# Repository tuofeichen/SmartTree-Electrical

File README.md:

# SmartTree Electrical System Design 
This repo contains the PCB design and Arduino code for the SmartTree electrical system. As a part of Engineers for a Sustainable World (ESW) at Northwestern, SmartTree is a student-run design project aimed to bring solar energy to Northwestern and get the community involved in sustainability. SmartTree provides a ‘trunk’ of solar-powered AC and USB outlets centered around a seating area, so anyone can bring his or her laptop or phone outside without having to worry about running low on battery. Having SmartTree on campus will not only allow students to best utilize technology outdoors, but also raise awareness for the potential solutions clean energy can bring to everyday life. Learn more about [ESW @ NU](http://www.eswnu.org/). 

The repo's directory is briefly described as below:

### Construction Documentation
contains the overall construction and design documentation, including hardware and software overview of the system. 

### BMS Software Documentation
contains the documentation for the battery management system software. It includes the design rationale of the software and some messaging protocal we use to communicate between the BMS board and the screen board. 

### PCB 
contains the PCB design of the battery management system (BMS) and the cell monitor unit (CMU), refer to the documentation for more details. 

### SmartTree Client
contains the client code of the software. The client is the microcontroller in charge of the screen update for the UI. It receives sensor data from the server and displays it on the screen. 

### SmartTree Server
contains the server code which controls and monitors the cell monitor unit and send out the information to the client for UI. 

### Testing
contains some the testing data logged on an SD card.

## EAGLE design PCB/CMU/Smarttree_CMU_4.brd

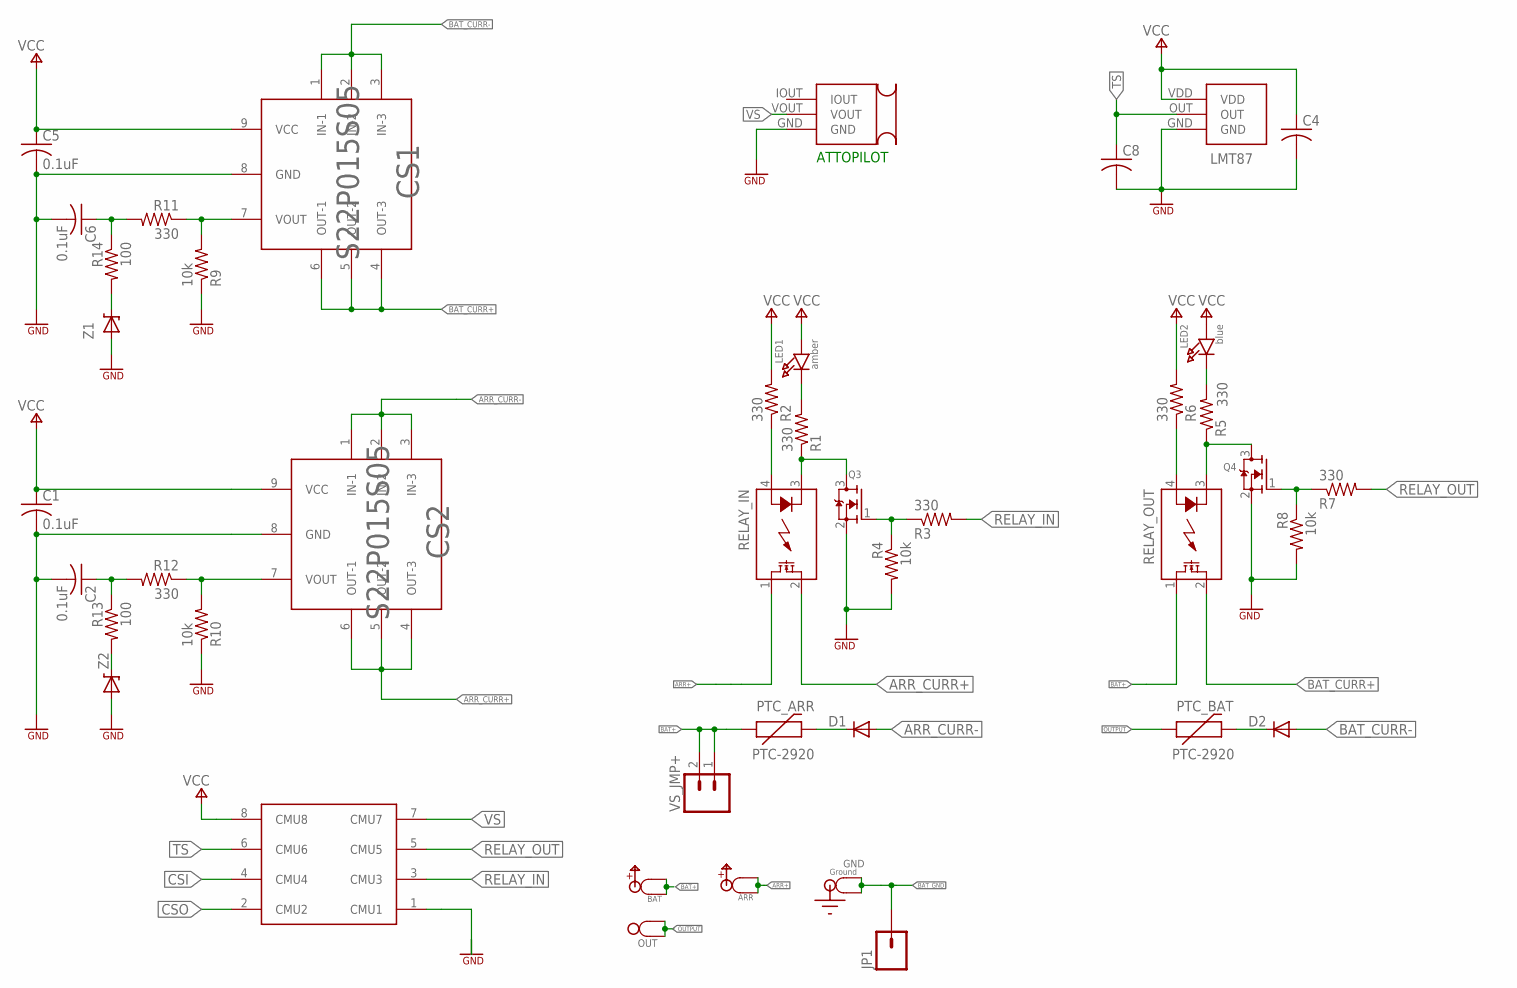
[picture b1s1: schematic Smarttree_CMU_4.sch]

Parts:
ARR: SPADE-POWER
ATTOPILOT: ATTOPILOT_VOLT; TH_BKOT
BAT: SPADE-POWER
C1, C2, C5, C6: 0.1uF; C0805
C4, C8: C-USC0805; C0805
CS1, CS2: S22P015S05
D1, D2: DIODE-SOD106-R; SOD106-R
GND: SPADE-GROUND
JP1: M01OFFSET; 1X01_OFFSET
LED1: amber; CHIPLED_0805
LED2: blue; CHIPLED_0805
LMT87: LMT87_PAC; LMT87_TO
OUT: SPADE-TERMINALPTH; SPADE-TERMINAL
PTC_ARR: PTC-2920
PTC_BAT: PTC-2920
Q3, Q4: MOSFET-NREFLOW; SOT23
R1, R2, R3, R5, R6, R7, R11, R12: 330; R0805
R4, R8, R9, R10: 10k; R0805
R13, R14: 100; R0805
RELAY_IN: CPC1708J; I4-PAC
RELAY_OUT: CPC1708J; I4-PAC
U$1: 8PINCONN
VS_JMP+: M02; 1X02_LONGPADS
Z1, Z2: DIODE-ZENER-BZT52; SOD-323

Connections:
ARR+: ARR.P$1, ARR.P$2, RELAY_IN.1 (DS1)
ARR_CURR+: CS2.4 (OUT-3), CS2.5 (OUT-2), CS2.6 (OUT-1), RELAY_IN.2 (DS2)
ARR_CURR-: CS2.1 (IN-1), CS2.2 (IN-2), CS2.3 (IN-3), D1.A
BAT+: BAT.P$1, BAT.P$2, PTC_ARR.1, RELAY_OUT.1 (DS1), VS_JMP+.1, VS_JMP+.2
BAT_CURR+: CS1.4 (OUT-3), CS1.5 (OUT-2), CS1.6 (OUT-1), RELAY_OUT.2 (DS2)
BAT_CURR-: CS1.1 (IN-1), CS1.2 (IN-2), CS1.3 (IN-3), D2.A
BAT_GND: GND.P$1, GND.P$2, JP1.1
CSI: C2.1, R12.2, R13.1, U$1.4 (CMU4)
CSO: C6.1, R11.2, R14.1, U$1.2 (CMU2)
GND: ATTOPILOT.GND, C1.2, C2.2, C4.2, C5.2, C6.2, C8.2, CS1.8 (GND), CS2.8 (GND), LMT87.GND, Q3.2 (S), Q4.2 (S), R4.2, R8.2, R9.1, R10.1, U$1.1 (CMU1), Z1.2 (A), Z2.2 (A)
unnamed: Q3.3 (D), R1.1, RELAY_IN.3 (K)
unnamed: Q4.3 (D), R5.1, RELAY_OUT.3 (K)
unnamed: LED1.C, R1.2
unnamed: R2.1, RELAY_IN.4 (A)
unnamed: LED2.C, R5.2
unnamed: Q3.1 (G), R3.1, R4.1
unnamed: R6.1, RELAY_OUT.4 (A)
unnamed: Q4.1 (G), R7.1, R8.1
unnamed: R13.2, Z2.1 (C)
unnamed: D2.C, PTC_BAT.2
unnamed: D1.C, PTC_ARR.2
unnamed: CS1.7 (VOUT), R9.2, R11.1
unnamed: CS2.7 (VOUT), R10.2, R12.1
unnamed: R14.2, Z1.1 (C)
OUTPUT: OUT.P$1, OUT.P$2, PTC_BAT.1
RELAY_IN: R3.2, U$1.3 (CMU3)
RELAY_OUT: R7.2, U$1.5 (CMU5)
TS: C8.1, LMT87.OUT, U$1.6 (CMU6)
VCC: C1.1, C4.1, C5.1, CS1.9 (VCC), CS2.9 (VCC), LED1.A, LED2.A, LMT87.VDD, R2.2, R6.2, U$1.8 (CMU8)
VS: ATTOPILOT.VOUT, U$1.7 (CMU7)

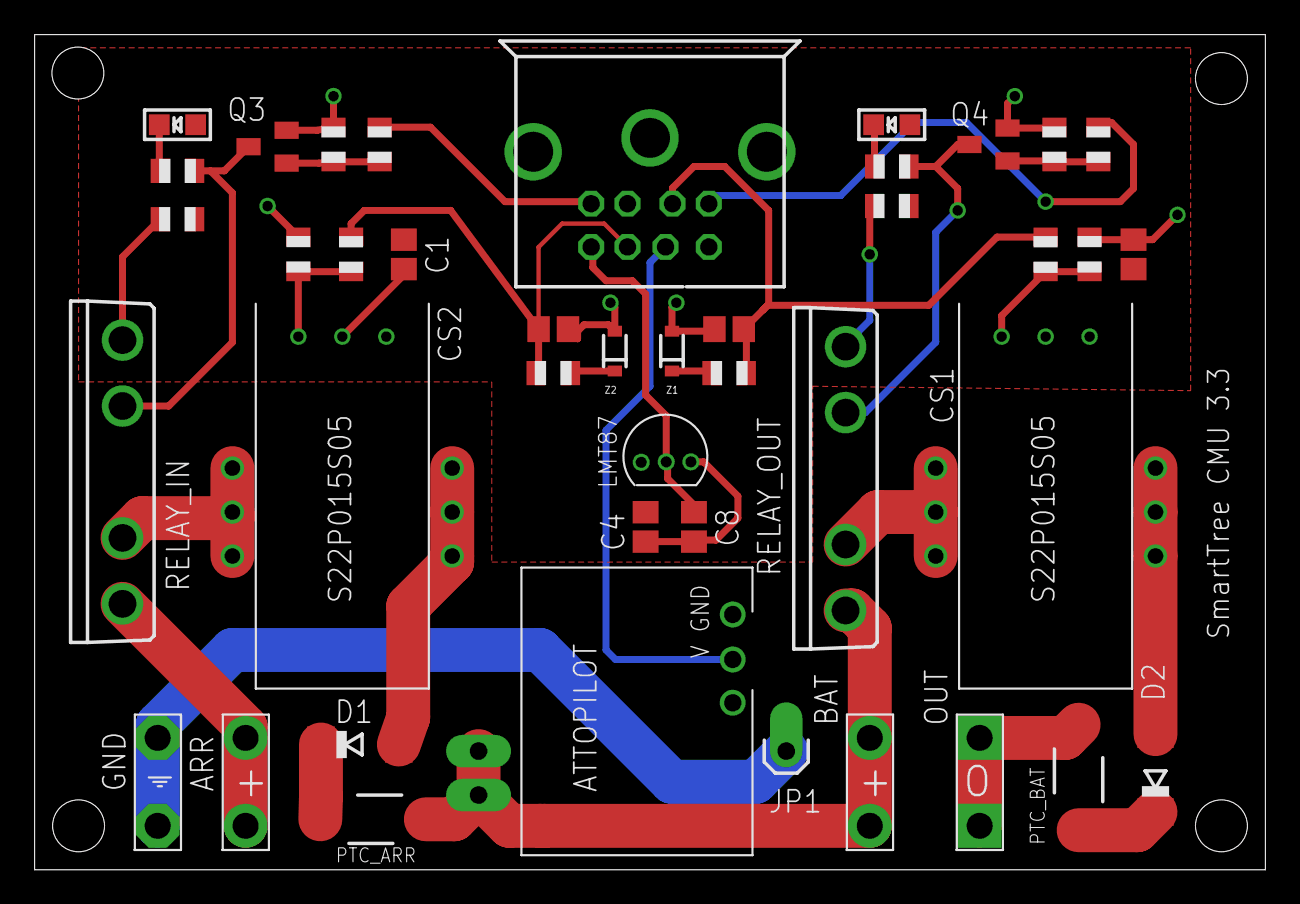
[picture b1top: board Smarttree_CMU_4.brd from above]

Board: 2 copper layers, 71.1 x 48.3 mm, 43 parts (0 on the bottom side), 30 nets.

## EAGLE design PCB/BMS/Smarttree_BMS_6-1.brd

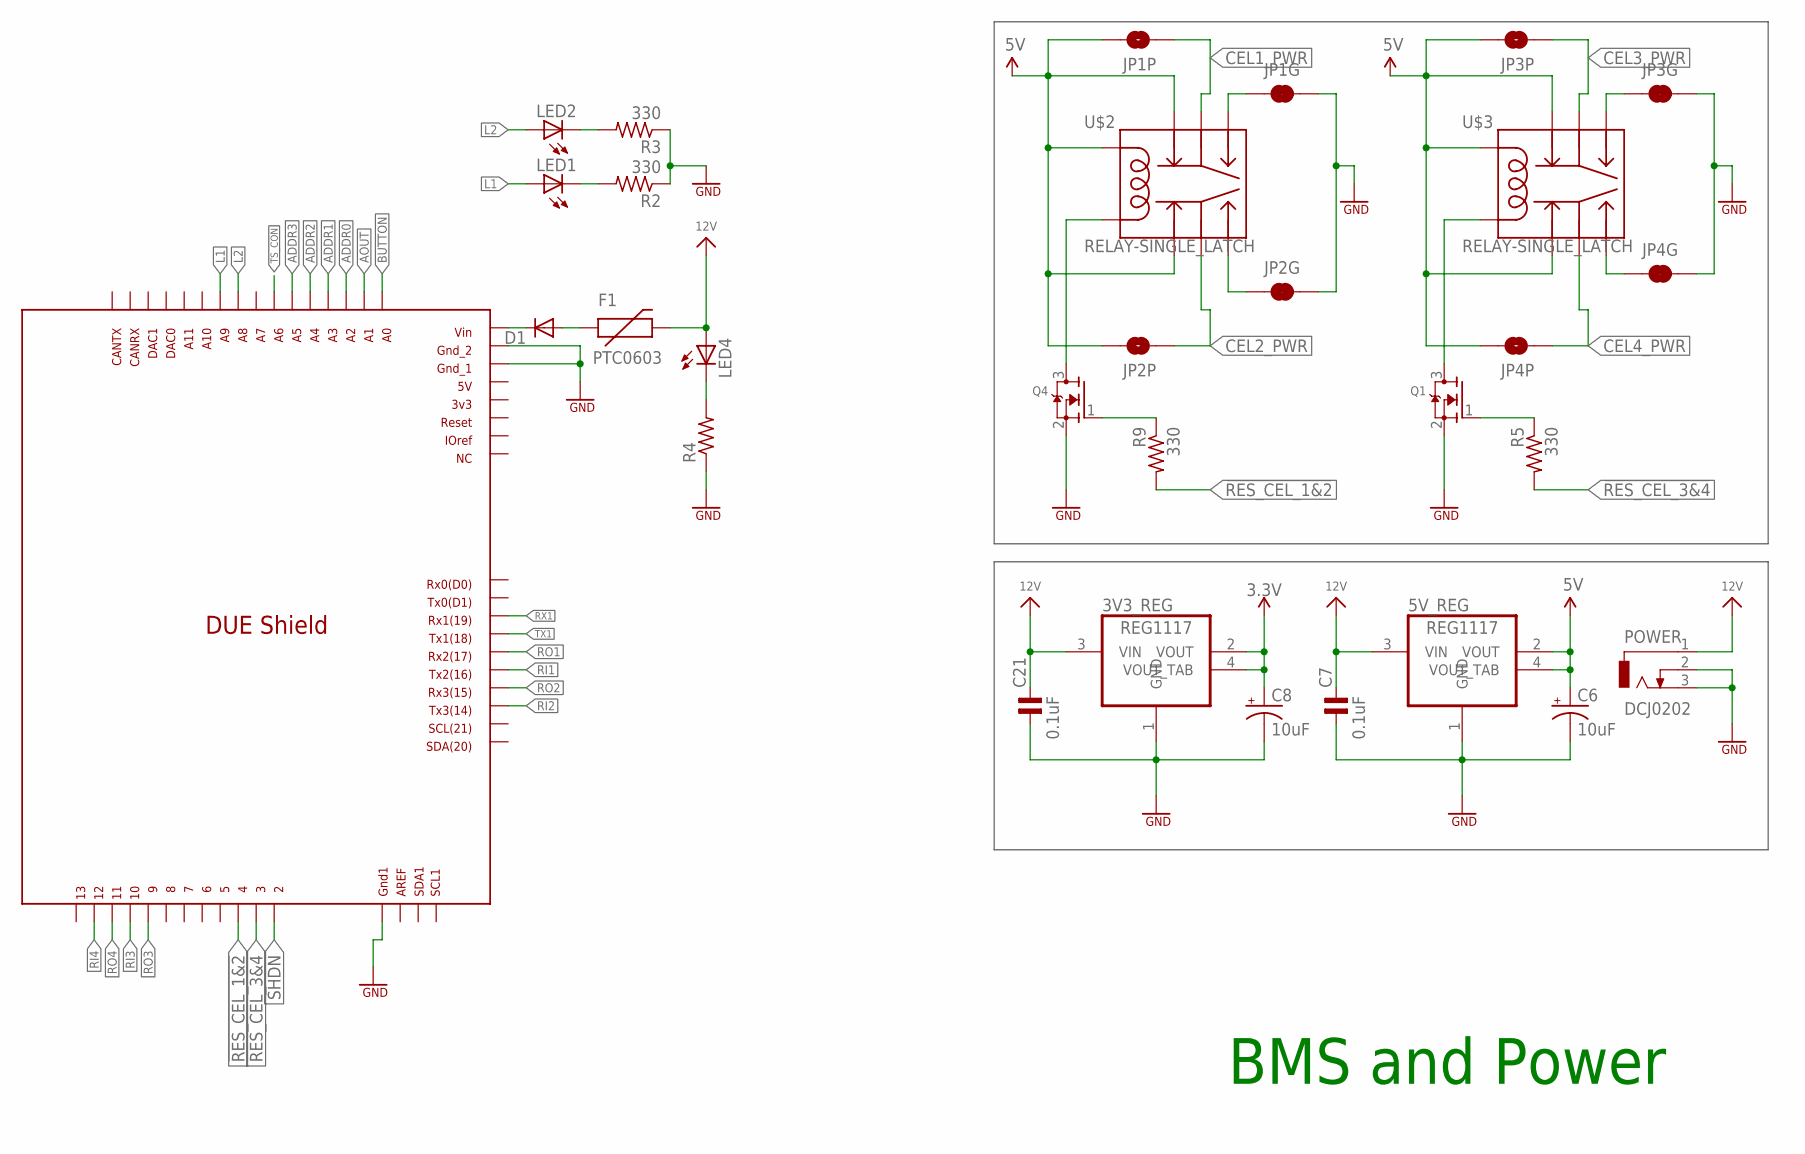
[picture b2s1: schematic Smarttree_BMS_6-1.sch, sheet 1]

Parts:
3V3_REG, 5V_REG: REG1117; SOT223
C6, C8: 10uF; EIA3216
C7, C21: 0.1uF; C-0805
D1: DIODE-SOD106-R; SOD106-R
F1: PTC0603; 0603
JP1G, JP2G, JP3G, JP4G: JUMPER-SMT_2_NC_TRACE_SILK; SMT-JUMPER_2_NC_TRACE_SILK
JP1P, JP2P, JP3P, JP4P: JUMPER-SMT_2_NO_SILK; SMT-JUMPER_2_NO_SILK
LED1, LED2, LED4: LED-YELLOW0603; LED-0603
POWER: DCJ0202
Q1, Q4: MOSFET-NREFLOW; SOT23
R2, R3: 330; M0805
R4: R-US_M0805; M0805
R5, R9: 330; R0805
U$1: DUE(OUTLINE); DUE(NORMAL)
U$2, U$3: RELAY-SINGLE_LATCH; RELAY-EE2

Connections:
3.3V: 3V3_REG.2 (VOUT), 3V3_REG.4 (VOUT_TAB), C8.A (+); also elsewhere on the board
5V: 5V_REG.2 (VOUT), 5V_REG.4 (VOUT_TAB), C6.A (+), JP1P.2, JP2P.2, JP3P.2, JP4P.2, U$2.P$1 (COIL1), U$2.P$3, U$2.P$10, U$3.P$1 (COIL1), U$3.P$3, U$3.P$10; also elsewhere on the board
12V: 3V3_REG.3 (VIN), 5V_REG.3 (VIN), C7.2, C21.2, F1.2, LED4.A, POWER.1; also elsewhere on the board
!RES_CEL_1&2: R9.2, U$1.4
!RES_CEL_3&4: R5.2, U$1.3
ADDR0: U$1.A2; also elsewhere on the board
ADDR1: U$1.A3; also elsewhere on the board
ADDR2: U$1.A4; also elsewhere on the board
ADDR3: U$1.A5; also elsewhere on the board
AOUT: U$1.A1; also elsewhere on the board
BUTTON: U$1.A0
CEL1_PWR: JP1P.1, U$2.P$4; also elsewhere on the board
CEL2_PWR: JP2P.1, U$2.P$9; also elsewhere on the board
CEL3_PWR: JP3P.1, U$3.P$4; also elsewhere on the board
CEL4_PWR: JP4P.1, U$3.P$9; also elsewhere on the board
GND: 3V3_REG.1 (GND), 5V_REG.1 (GND), C6.C (-), C7.1, C8.C (-), C21.1, JP1G.2, JP2G.2, JP3G.2, JP4G.2, POWER.2, POWER.3, Q1.2 (S), Q4.2 (S), R2.1, R3.1, R4.1, U$1.GND1, U$1.GND_1, U$1.GND_2; also elsewhere on the board
L1: LED1.A, U$1.A9
L2: LED2.A, U$1.A8
unnamed: JP1G.1, U$2.P$5
unnamed: Q4.3 (D), U$2.P$12 (COIL12)
unnamed: Q4.1 (G), R9.1
unnamed: Q1.1 (G), R5.1
unnamed: Q1.3 (D), U$3.P$12 (COIL12)
unnamed: JP3G.1, U$3.P$5
unnamed: JP4G.1, U$3.P$8
unnamed: D1.C, U$1.VIN
unnamed: JP2G.1, U$2.P$8
unnamed: LED1.C, R2.2
unnamed: LED2.C, R3.2
unnamed: LED4.C, R4.2
unnamed: D1.A, F1.1
RI1: U$1.TX2; also elsewhere on the board
RI2: U$1.TX3; also elsewhere on the board
RI3: U$1.10; also elsewhere on the board
RI4: U$1.12; also elsewhere on the board
RO1: U$1.RX2; also elsewhere on the board
RO2: U$1.RX3; also elsewhere on the board
RO3: U$1.9; also elsewhere on the board
RO4: U$1.11; also elsewhere on the board
RX1: U$1.RX1; also elsewhere on the board
SHDN: U$1.2; also elsewhere on the board
TS_CON: U$1.A6; also elsewhere on the board
TX1: U$1.TX1; also elsewhere on the board

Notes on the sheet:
BMS and Power

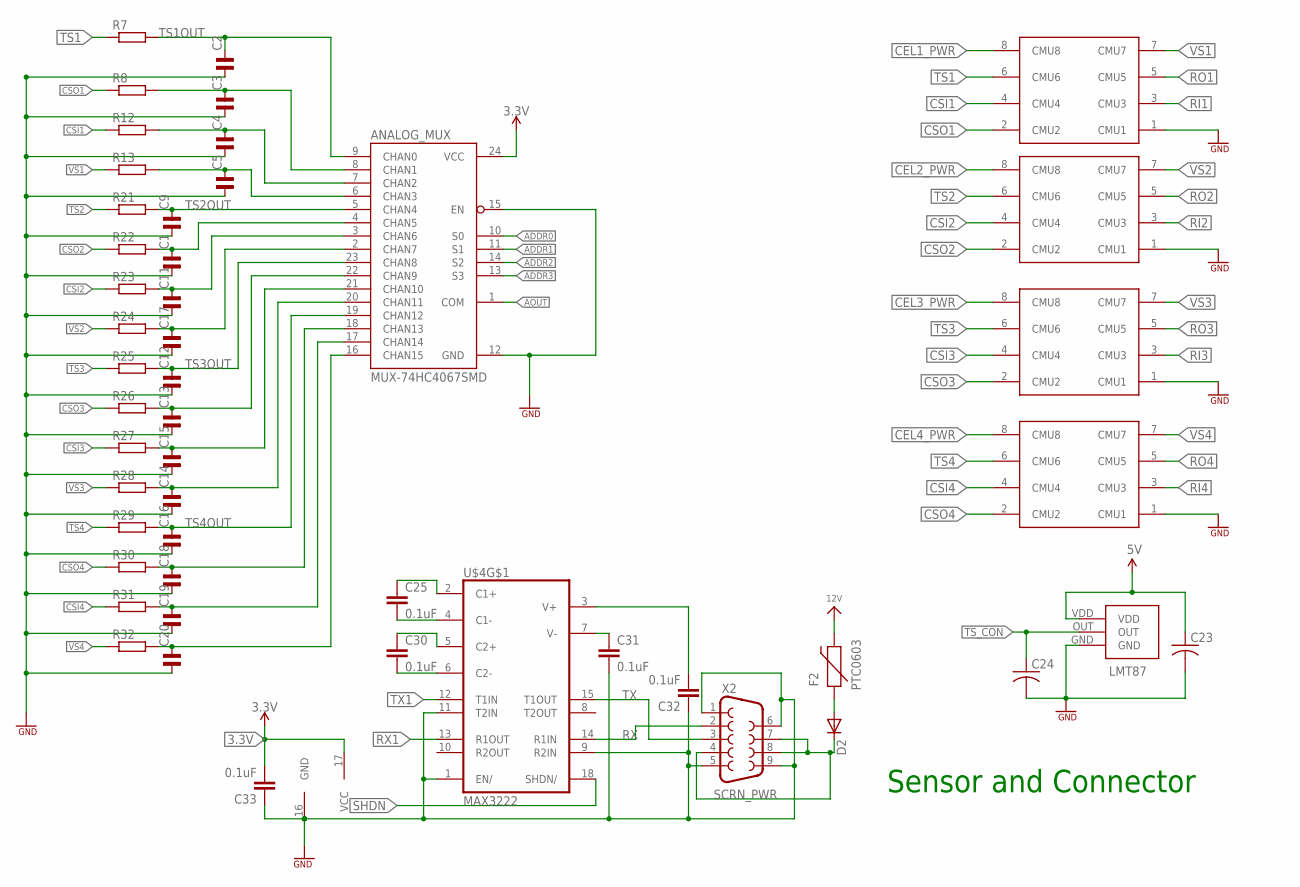
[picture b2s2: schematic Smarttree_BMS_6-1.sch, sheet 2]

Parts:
ANALOG_MUX: MUX-74HC4067SMD; SSOP24
C1, C2, C3, C4, C5, C9, C11, C12, C13, C14, C15, C16, C17, C18, C19, C20: C-NP-SMD-0805; C-0805
C23, C24: C-USC0805; C0805
C25, C30, C31, C32, C33: 0.1uF; 0603-CAP
CEL1, CEL2, CEL3, CEL4: 8PINCONN
D2: DIODE-SOD106-R; SOD106-R
F2: PTC0603; 0603
LMT87: LMT87_PAC; LMT87_TO
R7, R8, R12, R13, R21, R22, R23, R24, R25, R26, R27, R28, R29, R30, R31, R32: R-EU_R0805W; R0805W
U$4: MAX3222; SO18
X2: DB9MALE; DB9_MALE

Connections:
3.3V: ANALOG_MUX.24 (VCC), C33.2, U$4.17 (VCC); also elsewhere on the board
5V: C23.1, LMT87.VDD; also elsewhere on the board
12V: F2.2; also elsewhere on the board
ADDR0: ANALOG_MUX.10 (S0); also elsewhere on the board
ADDR1: ANALOG_MUX.11 (S1); also elsewhere on the board
ADDR2: ANALOG_MUX.14 (S2); also elsewhere on the board
ADDR3: ANALOG_MUX.13 (S3); also elsewhere on the board
AOUT: ANALOG_MUX.1 (COM); also elsewhere on the board
CEL1_PWR: CEL1.8 (CMU8); also elsewhere on the board
CEL2_PWR: CEL2.8 (CMU8); also elsewhere on the board
CEL3_PWR: CEL3.8 (CMU8); also elsewhere on the board
CEL4_PWR: CEL4.8 (CMU8); also elsewhere on the board
CSI1: CEL1.4 (CMU4), R12.1
CSI2: CEL2.4 (CMU4), R23.1
CSI3: CEL3.4 (CMU4), R27.1
CSI4: CEL4.4 (CMU4), R31.1
CSO1: CEL1.2 (CMU2), R8.1
CSO2: CEL2.2 (CMU2), R22.1
CSO3: CEL3.2 (CMU2), R26.1
CSO4: CEL4.2 (CMU2), R30.1
GND: ANALOG_MUX.12 (GND), ANALOG_MUX.15 (EN), C1.1, C2.1, C3.1, C4.1, C5.1, C9.1, C11.1, C12.1, C13.1, C14.1, C15.1, C16.1, C17.1, C18.1, C19.1, C20.1, C23.2, C24.2, C31.2, C32.1, C33.1, CEL1.1 (CMU1), CEL2.1 (CMU1), CEL3.1 (CMU1), CEL4.1 (CMU1), LMT87.GND, U$4.1 (EN/), U$4.9 (R2IN), U$4.11 (T2IN), U$4.16 (GND), X2.1, X2.5, X2.6, X2.9; also elsewhere on the board
unnamed: C31.1, U$4.7 (V-)
unnamed: D2.A, F2.1
unnamed: C25.1, U$4.2 (C1+)
unnamed: C25.2, U$4.4 (C1-)
unnamed: C30.1, U$4.5 (C2+)
unnamed: C30.2, U$4.6 (C2-)
unnamed: ANALOG_MUX.6 (CHAN3), C5.2, R13.2
unnamed: C32.2, U$4.3 (V+)
unnamed: ANALOG_MUX.8 (CHAN1), C3.2, R8.2
unnamed: ANALOG_MUX.7 (CHAN2), C4.2, R12.2
unnamed: ANALOG_MUX.4 (CHAN5), C1.2, R22.2
unnamed: ANALOG_MUX.3 (CHAN6), C11.2, R23.2
unnamed: ANALOG_MUX.2 (CHAN7), C17.2, R24.2
unnamed: ANALOG_MUX.22 (CHAN9), C13.2, R26.2
unnamed: ANALOG_MUX.21 (CHAN10), C15.2, R27.2
unnamed: ANALOG_MUX.20 (CHAN11), C14.2, R28.2
unnamed: ANALOG_MUX.18 (CHAN13), C18.2, R30.2
unnamed: ANALOG_MUX.17 (CHAN14), C19.2, R31.2
unnamed: ANALOG_MUX.16 (CHAN15), C20.2, R32.2
RI1: CEL1.3 (CMU3); also elsewhere on the board
RI2: CEL2.3 (CMU3); also elsewhere on the board
RI3: CEL3.3 (CMU3); also elsewhere on the board
RI4: CEL4.3 (CMU3); also elsewhere on the board
RO1: CEL1.5 (CMU5); also elsewhere on the board
RO2: CEL2.5 (CMU5); also elsewhere on the board
RO3: CEL3.5 (CMU5); also elsewhere on the board
RO4: CEL4.5 (CMU5); also elsewhere on the board
RX: U$4.14 (R1IN), X2.2
RX1: U$4.13 (R1OUT); also elsewhere on the board
SCRN_PWR: D2.C, X2.4, X2.7, X2.8
SHDN: U$4.18 (SHDN/); also elsewhere on the board
TS1: CEL1.6 (CMU6), R7.1
TS1OUT: ANALOG_MUX.9 (CHAN0), C2.2, R7.2
TS2: CEL2.6 (CMU6), R21.1
TS2OUT: ANALOG_MUX.5 (CHAN4), C9.2, R21.2
TS3: CEL3.6 (CMU6), R25.1
TS3OUT: ANALOG_MUX.23 (CHAN8), C12.2, R25.2
TS4: CEL4.6 (CMU6), R29.1
TS4OUT: ANALOG_MUX.19 (CHAN12), C16.2, R29.2
TS_CON: C24.1, LMT87.OUT; also elsewhere on the board
TX: U$4.15 (T1OUT), X2.3
TX1: U$4.12 (T1IN); also elsewhere on the board
VS1: CEL1.7 (CMU7), R13.1
VS2: CEL2.7 (CMU7), R24.1
VS3: CEL3.7 (CMU7), R28.1
VS4: CEL4.7 (CMU7), R32.1

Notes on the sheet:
Sensor and Connector

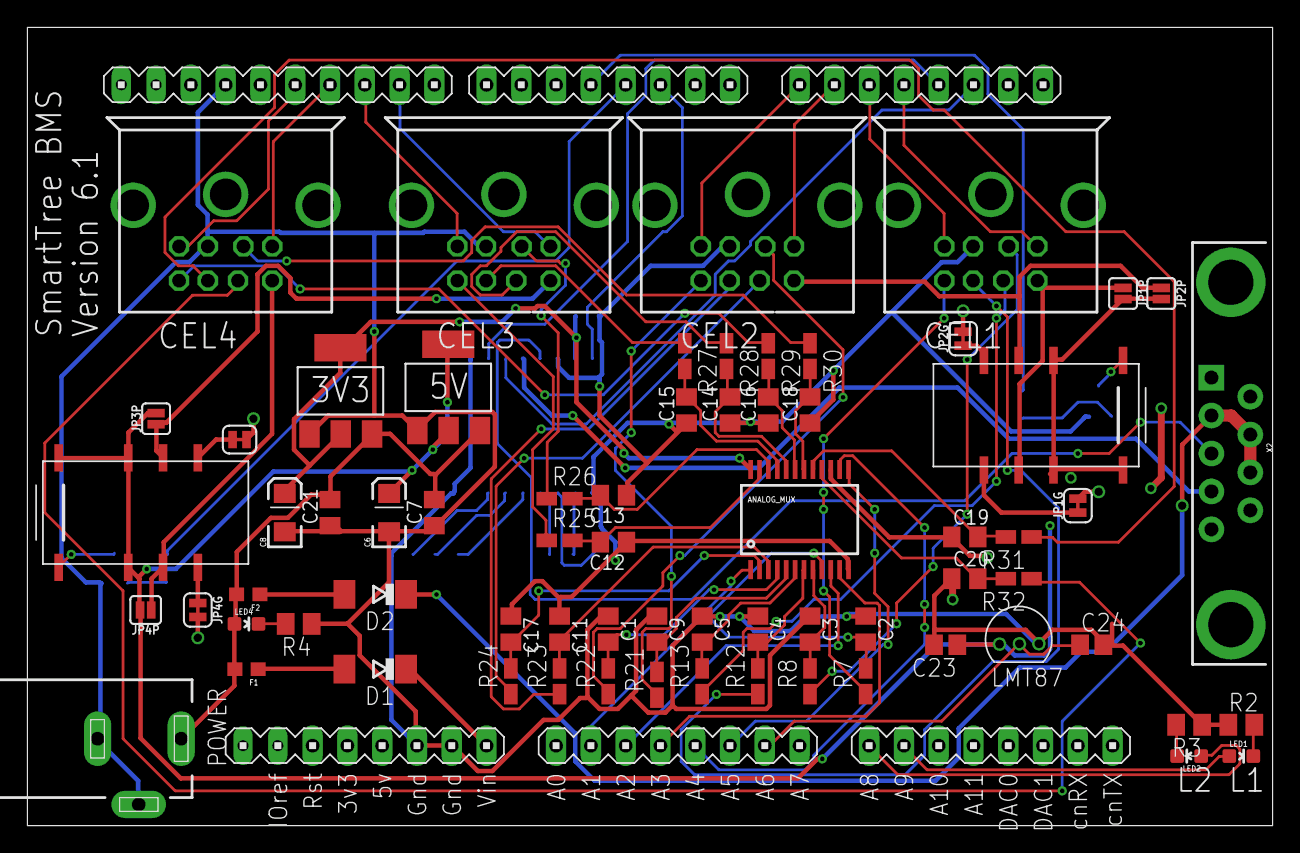
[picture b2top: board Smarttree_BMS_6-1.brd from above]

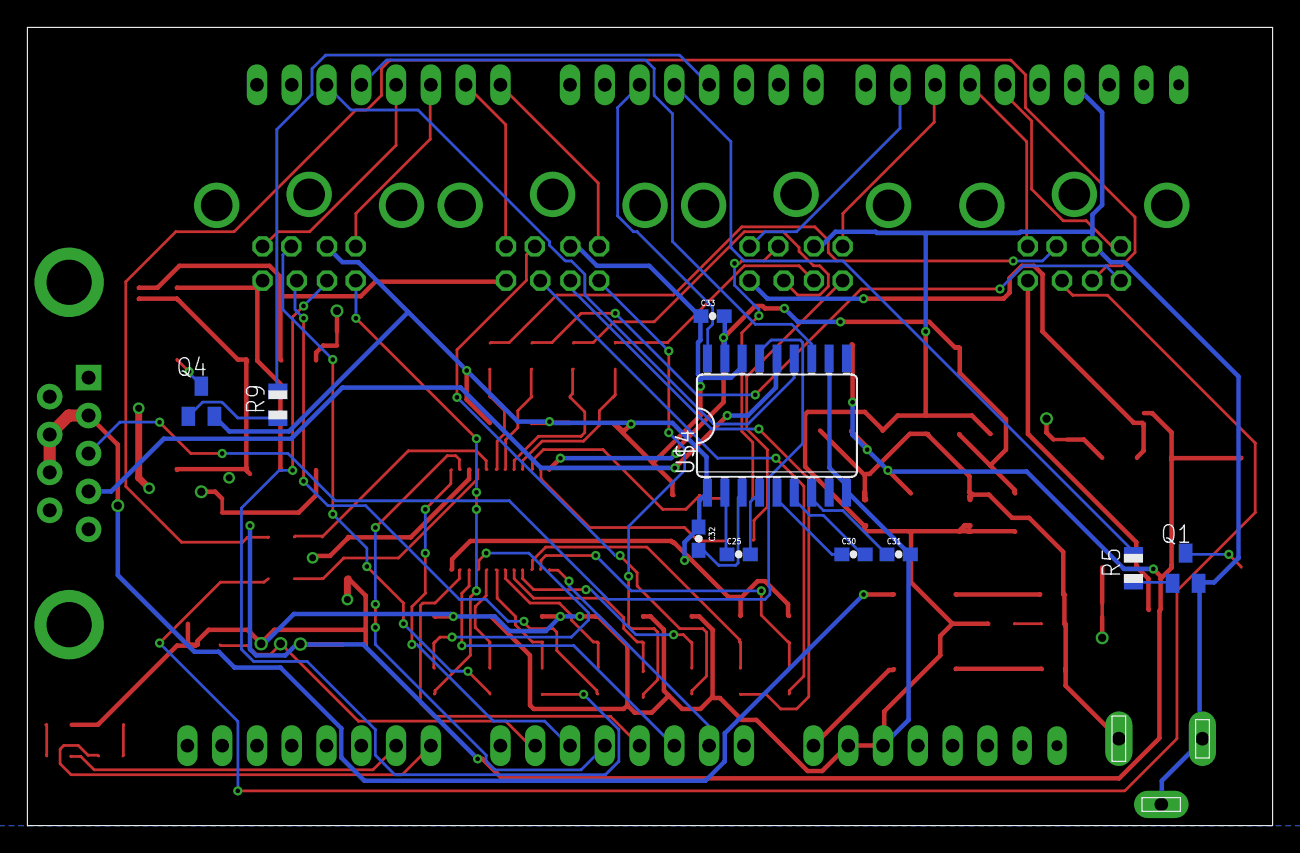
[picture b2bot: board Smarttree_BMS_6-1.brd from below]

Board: 2 copper layers, 90.9 x 58.3 mm, 79 parts (10 on the bottom side), 84 nets.

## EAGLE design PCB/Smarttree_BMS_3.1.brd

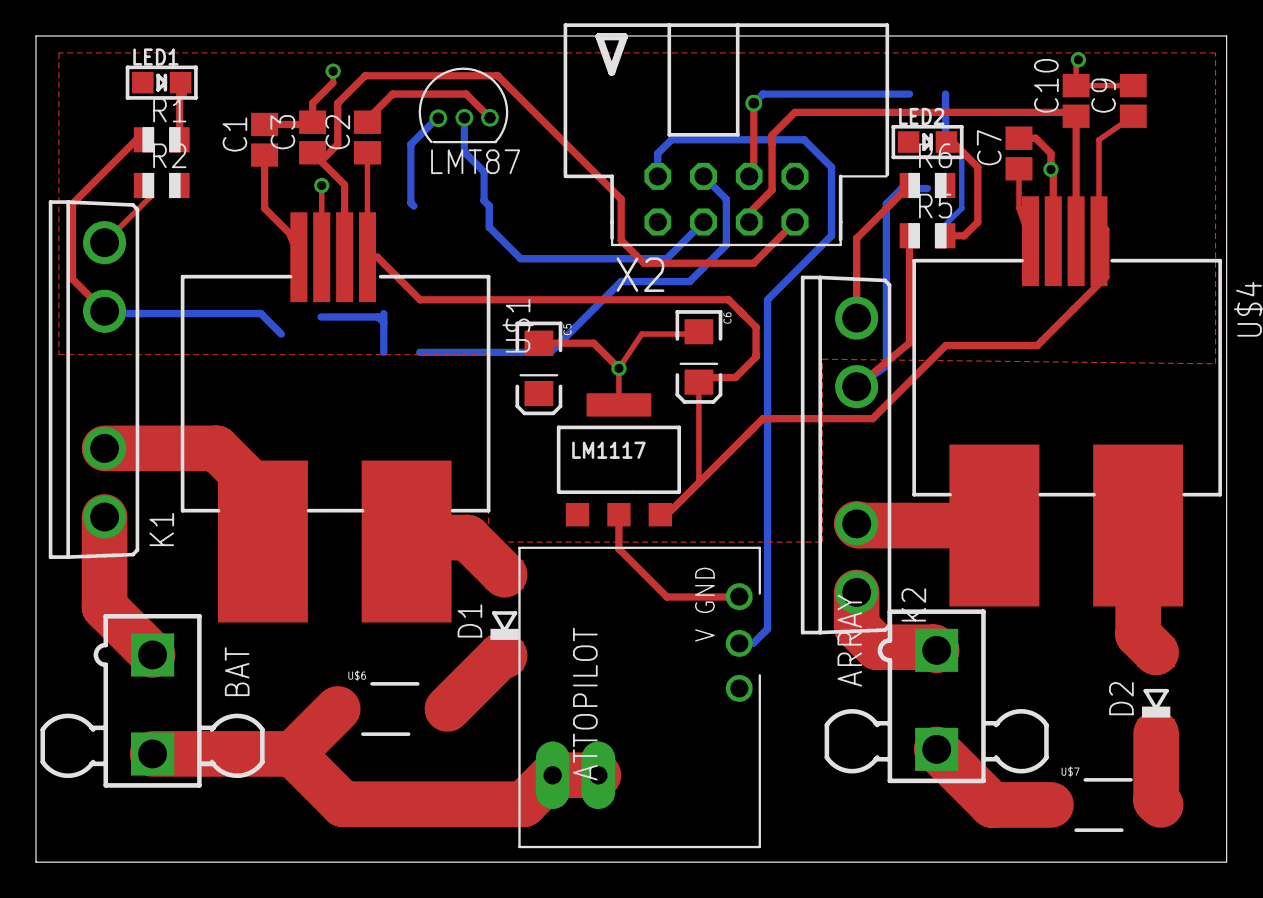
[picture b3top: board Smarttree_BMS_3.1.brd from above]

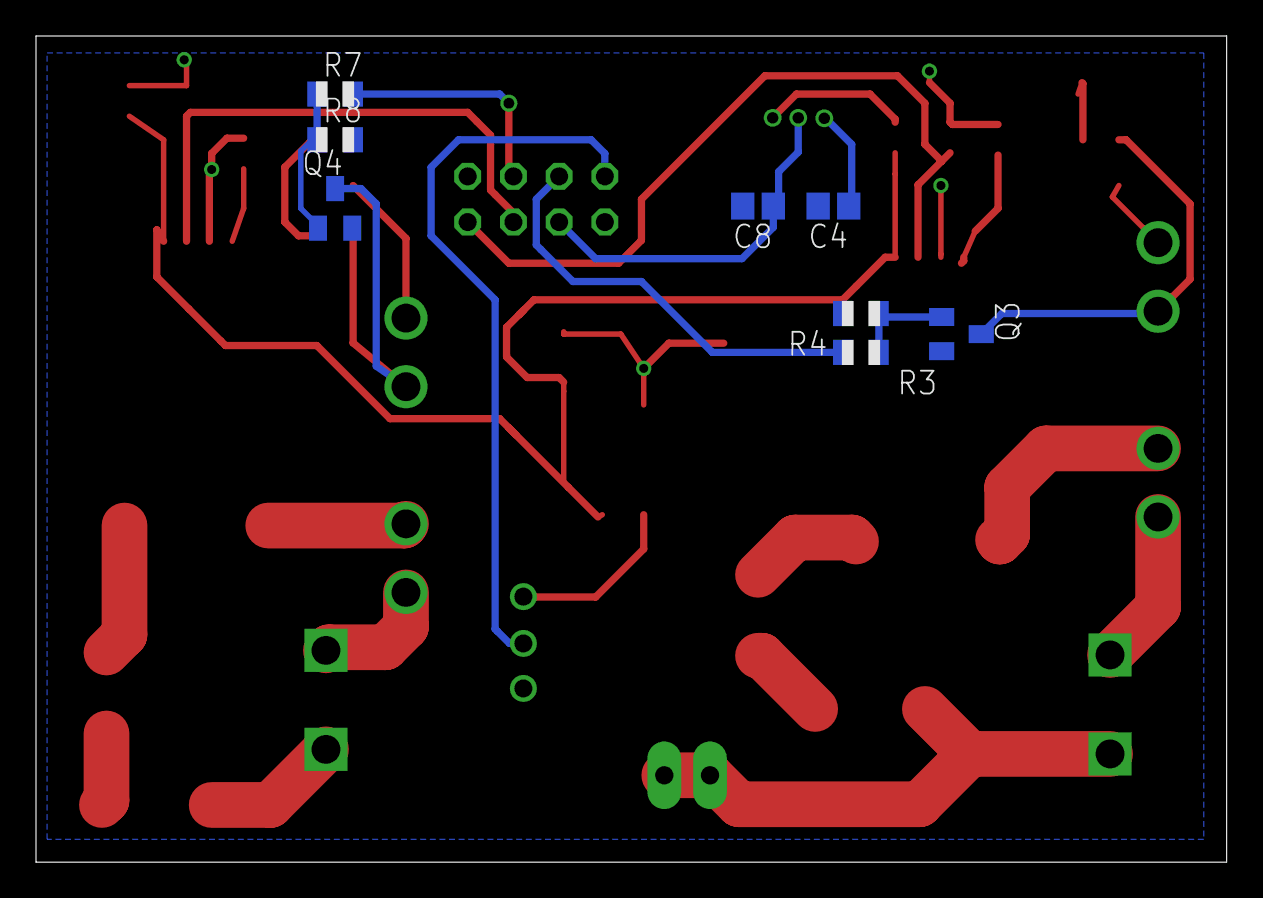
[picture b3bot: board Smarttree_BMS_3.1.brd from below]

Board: 2 copper layers, 66.1 x 45.9 mm, 37 parts (8 on the bottom side), 27 nets.

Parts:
ARRAY: 5566-2
ATTOPILOT: ATTOPILOT_VOLT; TH_BKOT
BAT: 5566-2
C1, C2, C7, C9: 47nF; C0805
C3, C10: 4.7nF; C0805
C4, C8: C0805
C5: 0.1uF; EIA3216
C6: 10uF; EIA3216
D1, D2: SOD106-R
K1, K2: CPC1708J; I4-PAC
LED1: amber; CHIPLED_0805
LED2: blue; CHIPLED_0805
LM1117: LM2937_SOT223; SOT223
LMT87: LMT87_PAC; LMT87_TO
Q3, Q4: SOT23
R1, R2, R3, R5, R6, R7: 330; R0805
R4, R8: 10k; R0805
U$1, U$4: HMS-5P-SOTA; SMD_CURR_SENSE
U$6, U$7: PTC-2920
VS_JMP: 1X02_LONGPADS
X2: 057-006-0

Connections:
2.5V: C2.1, C6.A, C9.1, LM1117.3, U$1.VREF, U$4.VREF
ARRAY+: D2.A, U$4.I+
ARRAY-: K2.2, U$4.I-
BAT+: D1.A, U$1.I+
BAT-: K1.2, U$1.I-
BATIN: BAT.1, K1.1
CSI: C10.1, U$4.OUTPUT, X2.5
CSO: C3.1, U$1.OUTPUT, X2.8
GND: ATTOPILOT.GND, C1.2, C2.2, C3.2, C4.2, C5.C, C6.C, C7.2, C8.2, C9.2, C10.2, LM1117.2, LM1117.4, LMT87.GND, Q3.2, Q4.2, R4.2, R8.2, U$1.GND, U$4.GND, X2.7
unnamed: K1.3, Q3.3, R1.1
unnamed: K2.3, Q4.3, R5.1
unnamed: LED1.C, R1.2
unnamed: K1.4, R2.1
unnamed: LED2.C, R5.2
unnamed: Q3.1, R3.1, R4.1
unnamed: K2.4, R6.1
unnamed: Q4.1, R7.1, R8.1
unnamed: BAT.2, U$6.1, VS_JMP.1, VS_JMP.2
unnamed: D2.C, U$7.2
unnamed: D1.C, U$6.2
unnamed: ARRAY.2, U$7.1
unnamed: ARRAY.1, K2.1
RELAY_IN: R7.2, X2.6
RELAY_OUT: R3.2, X2.4
TS: C8.1, LMT87.OUT, X2.3
VCC: C1.1, C4.1, C5.A, C7.1, LED1.A, LED2.A, LM1117.1, LMT87.VDD, R2.2, R6.2, U$1.VCC, U$4.VCC, X2.1
VS: ATTOPILOT.VOUT, X2.2

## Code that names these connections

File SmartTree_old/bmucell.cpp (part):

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void Cell::setup() {
  // set up shared ADC
  pinMode(ADCPIN, INPUT);
  pinMode(ADDR0, OUTPUT);
  pinMode(ADDR1, OUTPUT);
  pinMode(ADDR2, OUTPUT);
  pinMode(ADDR3, OUTPUT);
  analogReadResolution(12);

  pinMode(RSCREEN, OUTPUT);
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
Cell::Cell(unsigned int cellnum) {
  cell_num = cellnum;
  relay_in = relayInPin(cellnum);
  relay_out = relayOutPin(cellnum);
  pinMode(relay_in, OUTPUT);
  pinMode(relay_out, OUTPUT);
  digitalWrite(relay_in, HIGH);
  digitalWrite(relay_out, HIGH);

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
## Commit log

2016-07-18 clean up repo
2016-07-18 Server without submodule
2016-07-20 fix receiver serial1.begin location and add debug message
2016-07-22 fixed screen connection
2016-07-29 Screen communication fix: rogue pointer and resolve energy update location
2016-07-29 documentation
2016-08-01 add picture to installaion
2016-08-03 add pcb
2016-08-07 screen data transfer
2016-08-10 error message clean up and handling
2016-08-26 stable softwrae
2016-08-28 add libraries
2017-01-16 CMU board
    Add cmu board to the documentation
2017-01-29 stable screen functions
2017-01-29 reset Trip params
2017-01-30 add documentation
2017-01-30 test commit
2017-01-30 cleaned up code
2017-01-30 clean up server code
2017-01-30 server clean up
2017-03-06 comments about changes
2017-03-06 bms cnt'd
2017-03-29 add new pcb
2017-03-29 replace old CMU board
2017-04-02 test current sensor and relay
2017-04-05 bms(cmu)
2017-04-05 new cmu pcb
2017-04-05 gitignore garbage from eagle
2017-04-05 cmu(bms)
2017-04-08 gerber file and finalized cmu design
2017-04-13 working mode
2017-04-19 BMS with the new connectors
2017-04-20 cmu4
2017-04-20 rm old cmu;
2017-04-20 rename and arrange files
2017-04-20 new connector on cmu
2017-04-23 holes
2017-04-24 comp holes
2017-04-24 modified bms threshold
2017-04-26 bms final
2017-04-26 gerbers
2017-04-26 order files
2017-04-26 gerber cmu with new connector footprint
2017-04-27 clean up cmu folder
2017-05-02 finalized bms
2017-05-08 aesthetik fixes
2017-05-08 cleanup #b and #s and Gerber files
2017-05-08 new gerber
2017-05-08 bitmap
2017-05-10 revise resistor value for current sensor
2017-05-25 change logging timing
2017-05-28 add test data csv

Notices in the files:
parts and their libraries:
cap-pan40: Copyright (C) 2004, Bob Starr
SparkFun-Retired: Licensing:Creative Commons ShareAlike 4.0 International - https://creativecommons.org/licenses/by-sa/4.0
SparkFun: Licensing: CC v3.0 Share-Alike You are welcome to use this library for commercial purposes.
